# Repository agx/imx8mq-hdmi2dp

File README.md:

# HDMI to DP adapter for imx8mq

The imx8mq can output HDMI 2.0a or eDP/DP via it's HDMI TX. 
In order to test DisplayPort with a board that's designed
for HDMI one can use this adapter board. For this to work
you need to

- remove pull downs from the HDMI lanes. That's R1901-R1908 on the [Librem5 devkit][]
- use the DisplayPort instead of the HDMI firmware in uboot
  from https://www.nxp.com/lgfiles/NMG/MAD/YOCTO/firmware-imx-8.7.bin
- configure the Linux kernel for DP instead of HDMI for the cadence bridge
  as used in NXPs BSP:
  
```
&hdmi {
        compatible = "cdn,imx8mq-dp";
        lane-mapping = <0xc6>;
        status = "okay";
        port@1 {
                hdmi_in: endpoint {
                        remote-endpoint = <&dcss_out>;
                };
        };
};
```

The schematics for this kind of adapter were initially pubilshed by Bernhard
Fink from NXPs forum at https://community.nxp.com/thread/491629 .

[Librem5 devkit]: https://source.puri.sm/Librem5/dvk-mx8m-bsb

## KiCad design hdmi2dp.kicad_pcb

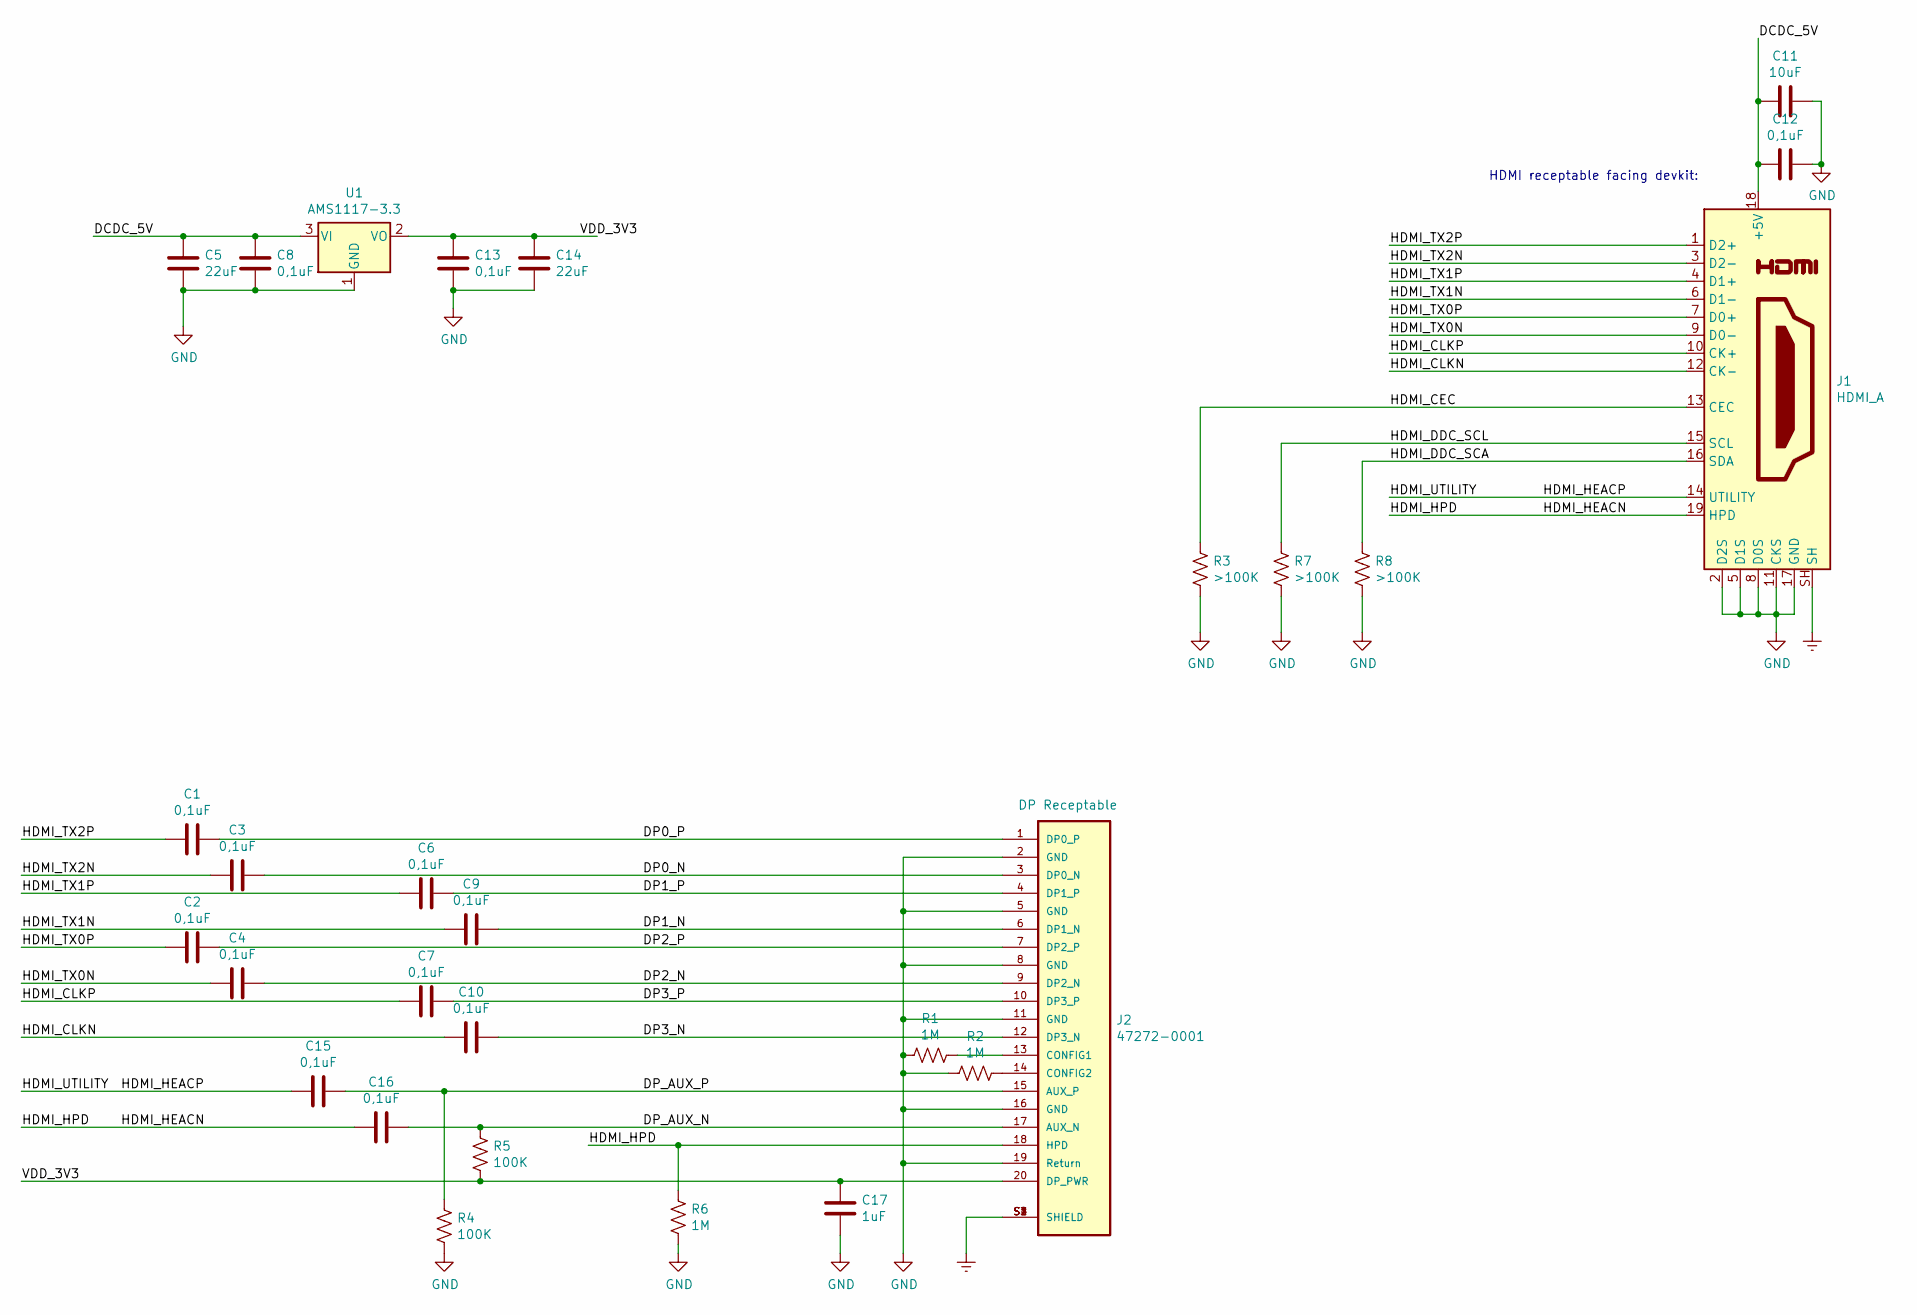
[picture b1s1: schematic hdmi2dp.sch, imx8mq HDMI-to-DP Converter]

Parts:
C1, C2, C3, C4, C6, C7, C8, C9, C10, C12, C13, C15, C16: 0,1uF; C_1206_3216Metric_Pad1.42x1.75mm_HandSolder
C5, C14: 22uF; C_1206_3216Metric_Pad1.42x1.75mm_HandSolder
C11: 10uF; C_1206_3216Metric_Pad1.42x1.75mm_HandSolder
C17: 1uF; C_1206_3216Metric_Pad1.42x1.75mm_HandSolder
J1: HDMI_A; AMPHENOL_10029449-001RLF
J2: 47272-0001; MOLEX_47272-0001
R1, R2, R6: 1M; R_1206_3216Metric_Pad1.42x1.75mm_HandSolder
R3, R7, R8: >100K; R_1206_3216Metric_Pad1.42x1.75mm_HandSolder
R4, R5: 100K; R_1206_3216Metric_Pad1.42x1.75mm_HandSolder
U1: AMS1117-3.3; SOT-223-3_TabPin2

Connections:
/DCDC_5V: C5.1, C8.1, C11.2, C12.2, J1.18 (+5V), U1.3 (VI)
/DP0_N: C3.1, J2.3 (DP0_N)
/DP0_P: C1.1, J2.1 (DP0_P)
/DP1_N: C9.1, J2.6 (DP1_N)
/DP1_P: C6.1, J2.4 (DP1_P)
/DP2_N: C4.1, J2.9 (DP2_N)
/DP2_P: C2.1, J2.7 (DP2_P)
/DP3_N: C10.1, J2.12 (DP3_N)
/DP3_P: C7.1, J2.10 (DP3_P)
/DP_AUX_N: C16.1, J2.17 (AUX_N), R5.1
/DP_AUX_P: C15.1, J2.15 (AUX_P), R4.1
/HDMI_CEC: J1.13 (CEC), R3.1
/HDMI_CLKN: C10.2, J1.12 (CK-)
/HDMI_CLKP: C7.2, J1.10 (CK+)
/HDMI_DDC_SCA: J1.16 (SDA), R8.1
/HDMI_DDC_SCL: J1.15 (SCL), R7.1
/HDMI_HEACN: C16.2, J1.19 (HPD), J2.18 (HPD), R6.1
/HDMI_HEACP: C15.2, J1.14 (UTILITY)
/HDMI_TX0N: C4.2, J1.9 (D0-)
/HDMI_TX0P: C2.2, J1.7 (D0+)
/HDMI_TX1N: C9.2, J1.6 (D1-)
/HDMI_TX1P: C6.2, J1.4 (D1+)
/HDMI_TX2N: C3.2, J1.3 (D2-)
/HDMI_TX2P: C1.2, J1.1 (D2+)
/VDD_3V3: C13.1, C14.1, C17.1, J2.20 (DP_PWR), R5.2, U1.2 (VO)
Earth: J1.S1, J1.S2, J1.S3, J1.S4, J1.SH, J2.S1 (SHIELD), J2.S2 (SHIELD), J2.S3 (SHIELD), J2.S4 (SHIELD)
GND: C5.2, C8.2, C11.1, C12.1, C13.2, C14.2, C17.2, J1.2 (D2S), J1.5 (D1S), J1.8 (D0S), J1.11 (CKS), J1.17 (GND), J2.2 (GND), J2.5 (GND), J2.8 (GND), J2.11 (GND), J2.16 (GND), J2.19 (Return), R1.2, R2.2, R3.2, R4.2, R6.2, R7.2, R8.2, U1.1 (GND)
unnamed: J2.13 (CONFIG1), R1.1
unnamed: J2.14 (CONFIG2), R2.1

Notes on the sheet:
HDMI receptable facing devkit:

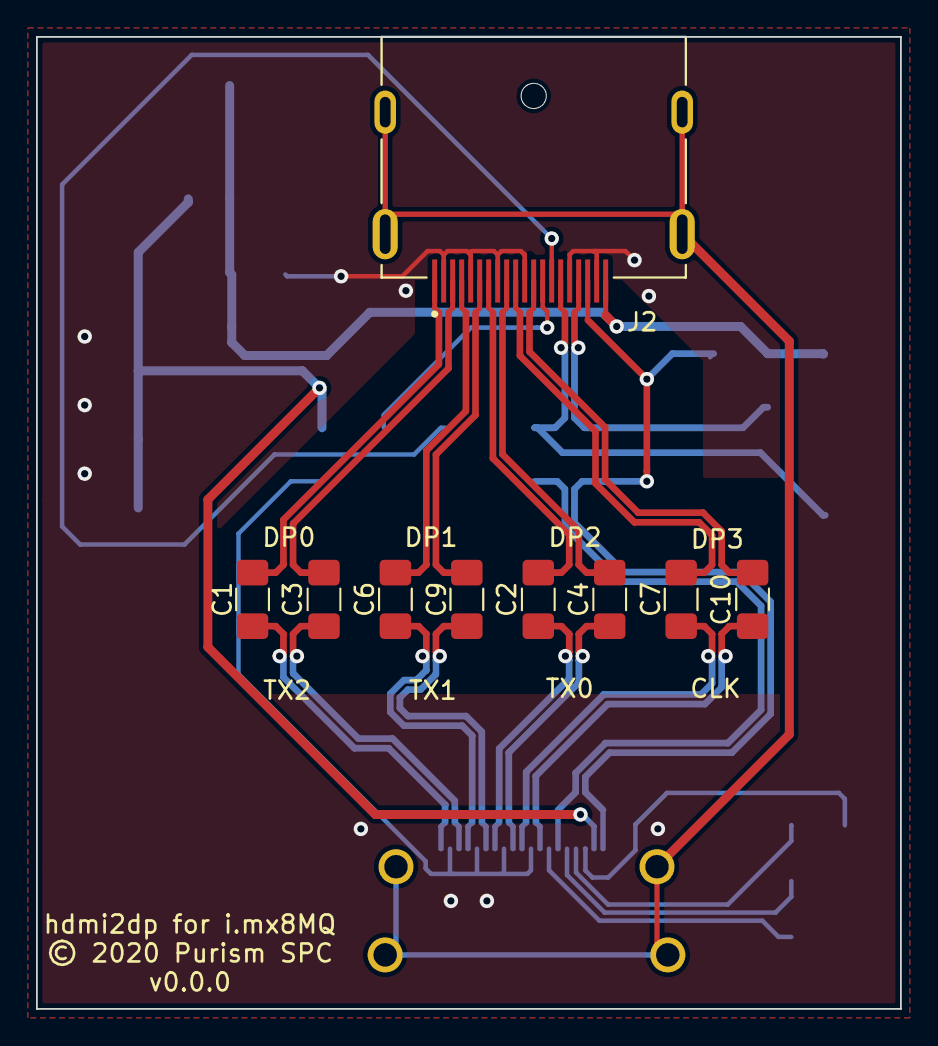
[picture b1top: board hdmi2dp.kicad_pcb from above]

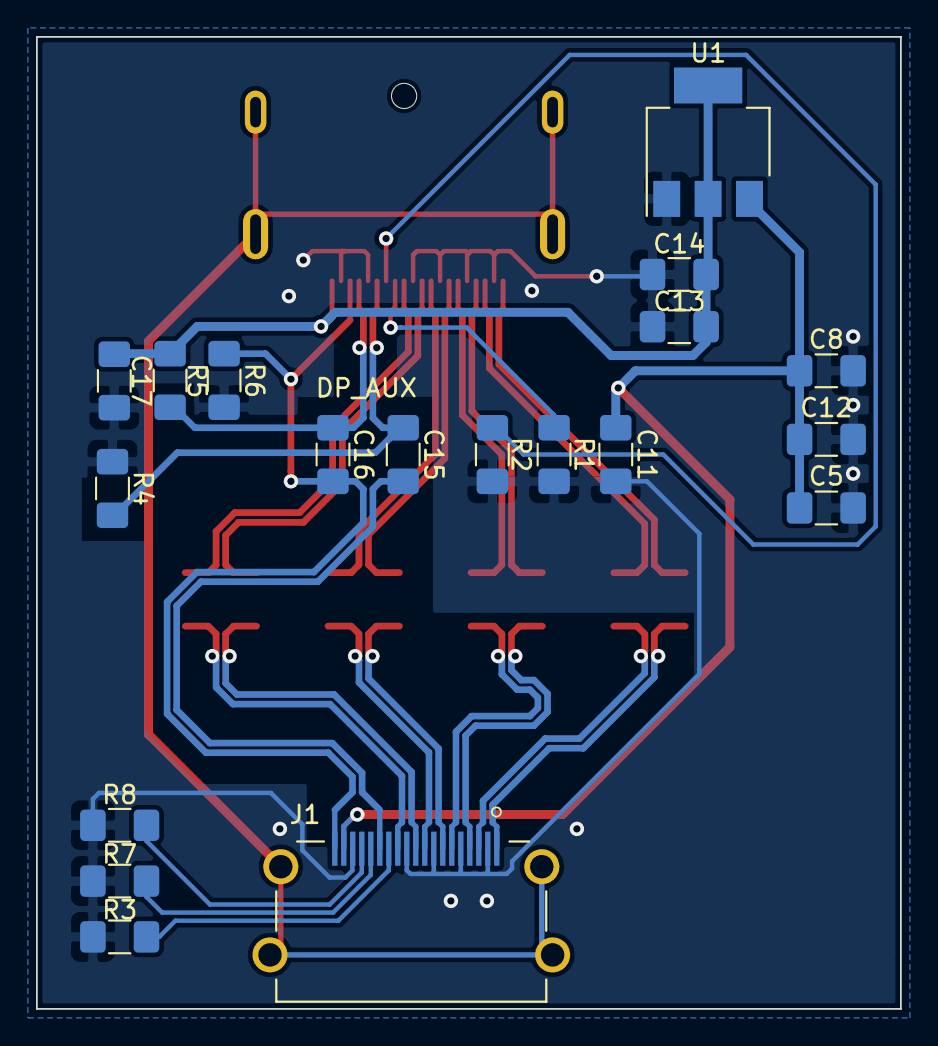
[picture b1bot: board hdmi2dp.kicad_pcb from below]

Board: 4 copper layers, 48.0 x 54.0 mm, 28 parts (19 on the bottom side), 29 nets.

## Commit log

2020-05-11 Reroute the diff pairs based on the impedance calculations using Beta Layout's stackup
    Also made the board 4 layers, fixed up the silkscreen, and added 3d models for the receptacles.
2020-05-26 Add README
    Document the steps to get this going
2020-05-26 Add copyright file
2020-05-27 Add HDMI and DP lane pair names to silk screen
2020-05-27 Add pdf

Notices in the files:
hdmi2dp.kicad_pcb:
© 2020 Purism SPC
hdmi2dp.sch:
License GPL3+
